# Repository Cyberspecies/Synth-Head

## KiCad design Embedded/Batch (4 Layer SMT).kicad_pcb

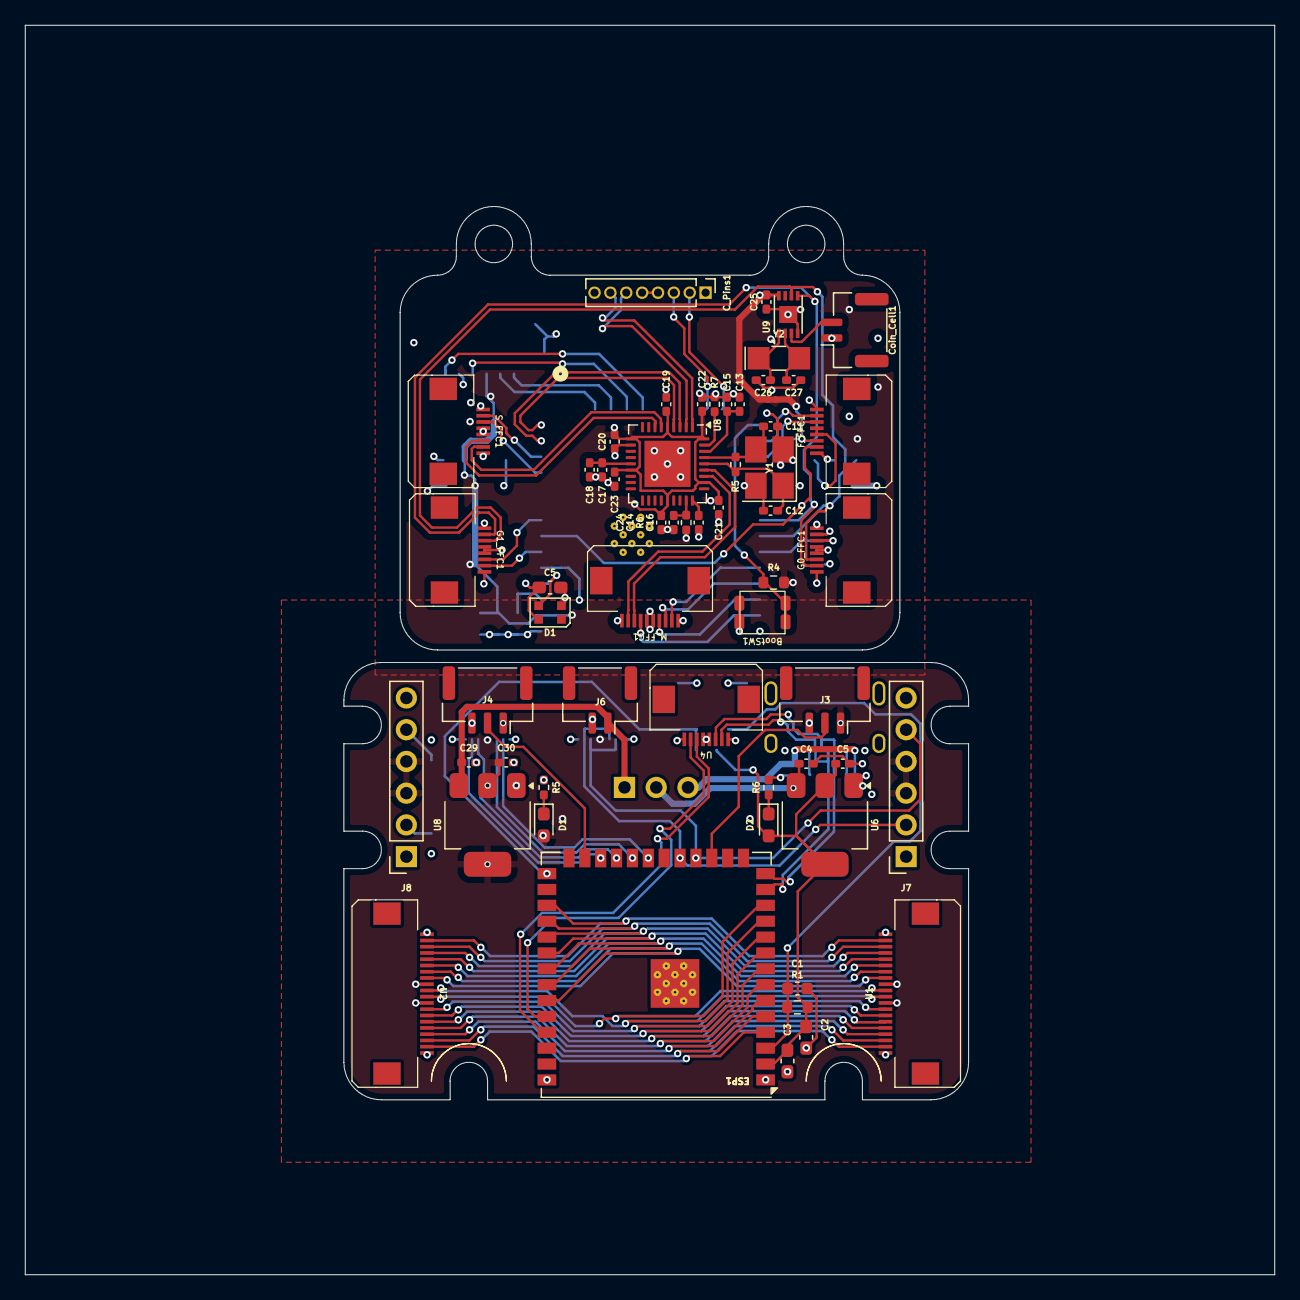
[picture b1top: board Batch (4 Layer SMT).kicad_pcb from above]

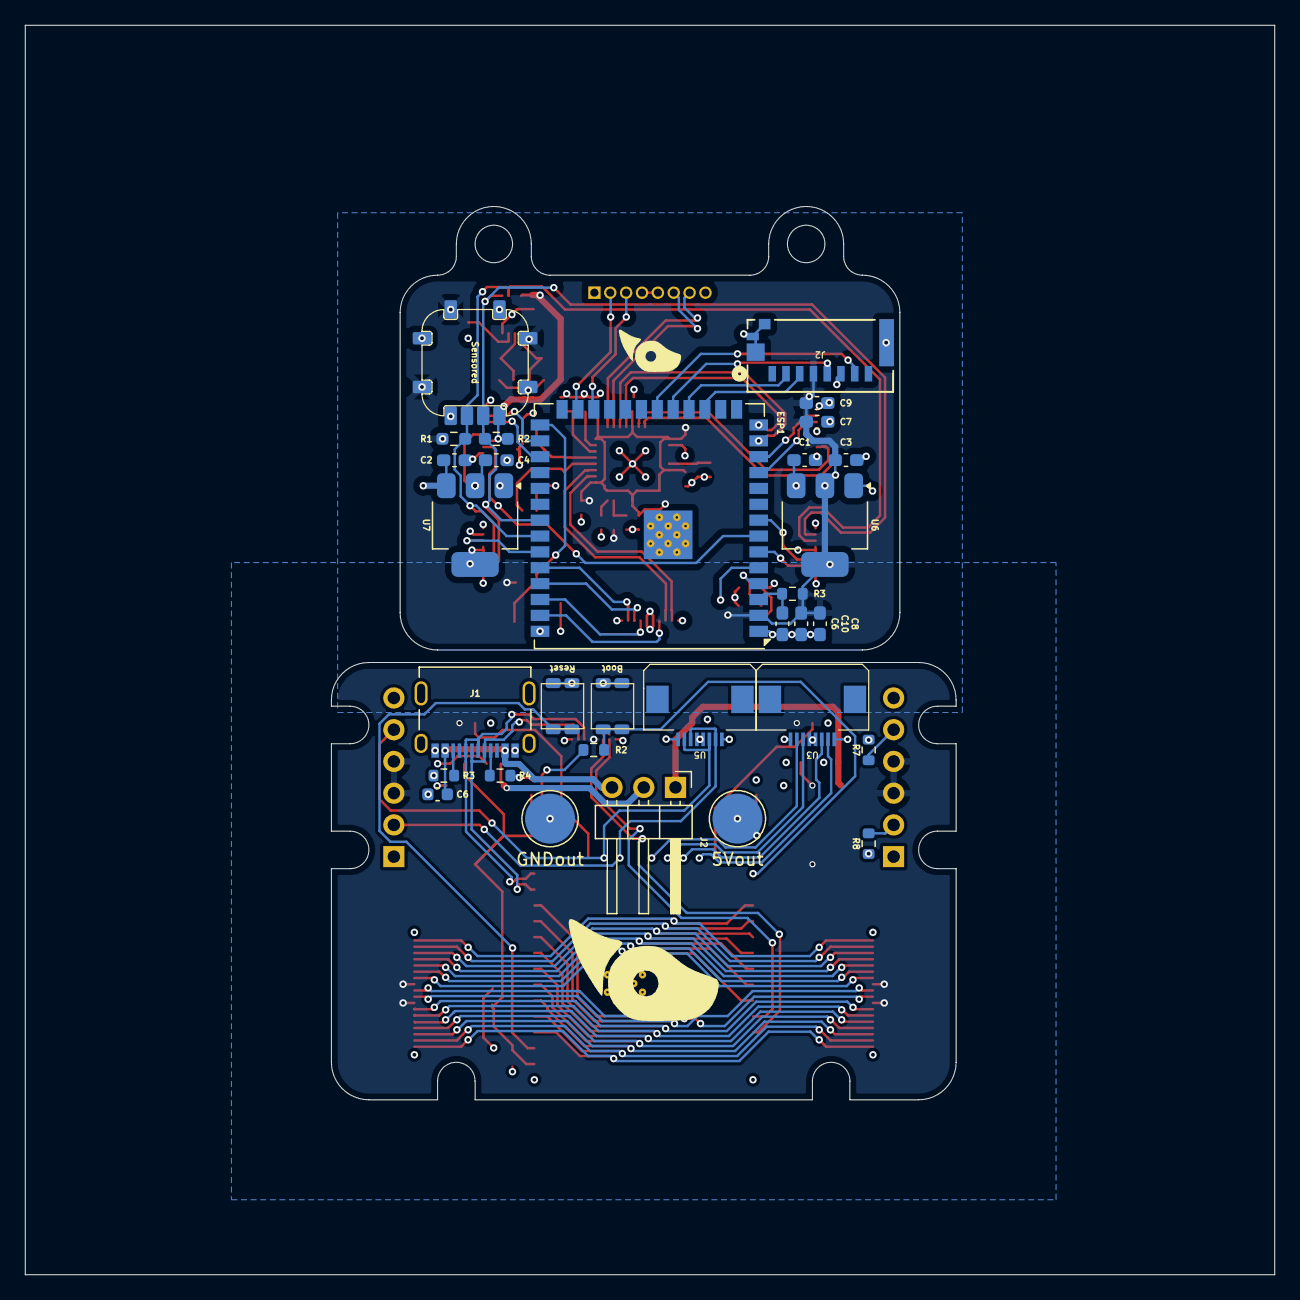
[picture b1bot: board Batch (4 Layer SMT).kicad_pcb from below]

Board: 4 copper layers, 100.0 x 100.0 mm, 89 parts (31 on the bottom side), 79 nets.

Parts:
BootSW1: SW_Push; R-667843
BootSW1#2: Boot; R-667843
C1: 1uF; C_0603_1608Metric
C1#2, C2#2: 0.1uf; C_0603_1608Metric_Pad1.08x0.95mm_HandSolder
C2, C7, C8: 22uF; C_0603_1608Metric_Pad1.08x0.95mm_HandSolder
C3, C9, C10: 0.1uF; C_0603_1608Metric_Pad1.08x0.95mm_HandSolder
C3#2, C4#2: 10uf; C_0603_1608Metric_Pad1.08x0.95mm_HandSolder
C4, C29: 0.1uf; C_0402_1005Metric_Pad0.74x0.62mm_HandSolder
C5, C30: 10uf; C_0402_1005Metric_Pad0.74x0.62mm_HandSolder
C5#2, C6: 1uF; C_0603_1608Metric_Pad1.08x0.95mm_HandSolder
C6#2: 10uF; C_0603_1608Metric
C11, C12: 18pf; C_0402_1005Metric_Pad0.74x0.62mm_HandSolder
C13, C17: 1uF; C_0402_1005Metric_Pad0.74x0.62mm_HandSolder
C14, C15, C16, C18, C19, C20, C21, C22, C23, C24, C25: 0.1uF; C_0402_1005Metric_Pad0.74x0.62mm_HandSolder
C26: 10pf; C_0402_1005Metric_Pad0.74x0.62mm_HandSolder
C27: 12pf; C_0402_1005Metric_Pad0.74x0.62mm_HandSolder
C_Pins1: C Pins; PinHeader_1x08_P1.27mm_Vertical
Coin_Cell1: Coin Cell; JST_GH_SM02B-GHS-TB_1x02-1MP_P1.25mm_Horizontal
D1, D2: LED; D_0603_1608Metric_Pad1.05x0.95mm_HandSolder
D1#2: WS2812B-2020; LED_WS2812B-2020_PLCC4_2.0x2.0mm
ESP1: ESP32-S3-WROOM-1; ESP32-S3-WROOM-1U
ESP1#2: ESP32-S3-WROOM-1U
F_FFC1: F FFC; FFC-8-0.5
G0_FFC1: G0 FFC; FFC-8-0.5
G1_FFC1: G1 FFC; FFC-8-0.5
J1: 10171746-00021LF; AMPHENOL_10171746-00021LF
J2: PWR Jumper Pins; PinHeader_1x03_P2.54mm_Horizontal
J2#2: MicroSD; MicroSD_473092651
J3: L0 JST; JST_GH_SM03B-GHS-TB_1x03-1MP_P1.25mm_Horizontal
J4: L1 JST; JST_GH_SM03B-GHS-TB_1x03-1MP_P1.25mm_Horizontal
J5: 5Vout; TestPoint_Pad_D4.0mm
J6: A JST; JST_GH_SM02B-GHS-TB_1x02-1MP_P1.25mm_Horizontal
J7: S Pins A; PinSocket_1x06_P2.54mm_Vertical
J8: S Pins B; PinSocket_1x06_P2.54mm_Vertical
J9: GNDout; TestPoint_Pad_D4.0mm
M_FFC1: M FFC; FFC-10-0.5
R1, R2#2, R3, R4: 10K; R_0603_1608Metric
R1#2, R2: 10K; R_0603_1608Metric_Pad0.98x0.95mm_HandSolder
R3#2, R4#2, R7#2, R8: 5.1K; R_0603_1608Metric
R5: 155ohm min; R_0402_1005Metric_Pad0.72x0.64mm_HandSolder
R5#2: 1M; R_0402_1005Metric_Pad0.72x0.64mm_HandSolder
R6: 100K; R_0402_1005Metric_Pad0.72x0.64mm_HandSolder
R6#2: 70ohm min; R_0402_1005Metric_Pad0.72x0.64mm_HandSolder
R7: 12K; R_0402_1005Metric_Pad0.72x0.64mm_HandSolder
RstSW1: Reset; R-667843
S_FFC1: S FFC; FFC-8-0.5
U1: D0 FFC; FFC-20-0.5
U2: D1 FFC; FFC-20-0.5
U3: U FFC; FFC-8-0.5
U4: S FFC; FFC-8-0.5
U5: R FFC; FFC-8-0.5
U6, U6#2: LD1117S33TR_SOT223; SOT-223-3_TabPin2
U7, U8#2: LD1117S50TR_SOT223; SOT-223-3_TabPin2
U8: USB2513B_Bi; QFN-36-1EP_6x6mm_P0.5mm_EP3.7x3.7mm
U9: MCP7940N-xMNY; DFN-8-1EP_3x2mm_P0.5mm_EP1.36x1.46mm
U11: Sensored
Y1: TSX-3225 24MF18X-C0; Crystal_SMD_SeikoEpson_TSX3225-4Pin_3.2x2.5mm_HandSoldering
Y2: CM7V-T1A; Crystal_SMD_MicroCrystal_CC7V-T1A-2Pin_3.2x1.5mm_HandSolder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

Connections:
+3V3: C2.1, C3.1, C3#2.1, C5.1, C7.1, C8.1, C9.1, C10.1, C19.1, C20.1, C21.1, C22.1, C23.1, C24.1, C25.1, D2.2 (A), ESP1.2 (3V3), ESP1#2.2 (3V3), F_FFC1.3, J2#2.4, R1.1, R1#2.1, R2.1, R2#2.1, R3.1, R4.1, R6.2, U6.2 (VO), U6#2.2 (VO), U8.5 (VDDA33), U8.10 (VDDA33), U8.15 (VDD33), U8.23 (VDD33), U8.29 (VDDA33), U8.36 (VDDA33), U9.8 (VCC), U11.3V3
+5V: C4#2.1, C5#2.1, C30.1, C_Pins1.4, C_Pins1.5, D1.2 (A), D1#2.4 (VDD), F_FFC1.4, F_FFC1.5, G0_FFC1.4, G0_FFC1.5, G1_FFC1.4, G1_FFC1.5, J3.1, J4.1, J5.1, J7.3, J7.4, J8.3, J8.4, S_FFC1.4, S_FFC1.5, U1.9, U1.12, U2.9, U2.12, U3.4, U3.5, U4.4, U4.5, U5.4, U5.5, U7.2 (VO), U8#2.2 (VO)
+5VP: C16.1, U8.27 (VBUS_DET)
+5VS: C1#2.1, C2#2.1, M_FFC1.5, M_FFC1.6, U6#2.3 (VI), U7.3 (VI)
+5VUSB: C6#2.1, J1.A4_B9 (VBUS_A), J1.B4_A9 (VBUS_B), J2.3
+PWR: C4.1, J2.2, U6.3 (VI)
+RAWVS: C29.1, J2.1, J6.1, U8#2.3 (VI)
Addr LED 0: ESP1.17 (GPIO9/TOUCH9/ADC1_CH8/FSPIHD/SUBSPIHD), J3.2
Addr LED 1: ESP1.25 (GPIO48/SPICLK_N/SUBSPICLK_N_DIFF), J4.2
Debug LED: D1#2.3 (DIN), ESP1#2.4 (GPIO4/TOUCH4/ADC1_CH3)
Disp GPIO 0: ESP1.4 (GPIO4/TOUCH4/ADC1_CH3), U1.2, U2.19
Disp GPIO 1: ESP1.5 (GPIO5/TOUCH5/ADC1_CH4), U1.3, U2.18
Disp GPIO 2: ESP1.6 (GPIO6/TOUCH6/ADC1_CH5), U1.4, U2.17
Disp GPIO 3: ESP1.7 (GPIO7/TOUCH7/ADC1_CH6), U1.5, U2.16
Disp GPIO 4: ESP1.8 (GPIO15/U0RTS/ADC2_CH4/XTAL_32K_P), U1.6, U2.15
Disp GPIO 5: ESP1.9 (GPIO16/U0CTS/ADC2_CH5/XTAL_32K_N), U1.7, U2.14
Disp GPIO 6: ESP1.10 (GPIO17/U1TXD/ADC2_CH6), U1.8, U2.13
Disp GPIO 7: ESP1.11 (GPIO18/U1RXD/ADC2_CH7/CLK_OUT3), U1.10, U2.10
Disp GPIO 8: ESP1.12 (GPIO8/TOUCH8/ADC1_CH7/SUBSPICS1), U1.11, U2.11
Disp GPIO 9: ESP1.35 (MTMS/GPIO42), U1.13, U2.8
Disp GPIO 10: ESP1.34 (MTDI/GPIO41/CLK_OUT1), U1.14, U2.7
Disp GPIO 11: ESP1.33 (MTDO/GPIO40/CLK_OUT2), U1.15, U2.6
Disp GPIO 12: ESP1.32 (MTCK/GPIO39/CLK_OUT3/SUBSPICS1), U1.16, U2.5
Disp GPIO 13: ESP1.31 (GPIO38/FSPIWP/SUBSPIWP), U1.17, U2.4
Disp GPIO 14: ESP1.30 (SPIDQS/GPIO37/FSPIQ/SUBSPIQ), U1.18, U2.3
Disp GPIO 15: ESP1.29 (SPIIO7/GPIO36/FSPICLK/SUBSPICLK), U1.19, U2.2
Fan 0: ESP1#2.29 (SPIIO7/GPIO36/FSPICLK/SUBSPICLK), F_FFC1.6
Fan 1: ESP1#2.28 (SPIIO6/GPIO35/FSPID/SUBSPID), F_FFC1.7
GND: BootSW1.2, BootSW1#2.2, C1.1, C1#2.2, C2.2, C2#2.2, C3.2, C3#2.2, C4.2, C4#2.2, C5.2, C5#2.2, C6.1, C6#2.2, C7.2, C8.2, C9.2, C10.2, C11.1, C12.1, C13.2, C14.2, C15.2, C16.2, C17.2, C18.2, C19.2, C20.2, C21.2, C22.2, C23.2, C24.2, C25.2, C26.2, C27.2, C29.2, C30.2, C_Pins1.1, C_Pins1.8, Coin_Cell1.1, D1#2.2 (VSS), ESP1.1 (GND), ESP1.40 (GND), ESP1.41 (GND), ESP1#2.1 (GND), ESP1#2.40 (GND), ESP1#2.41 (GND), F_FFC1.1, F_FFC1.8, G0_FFC1.1, G0_FFC1.8, G1_FFC1.1, G1_FFC1.8, J1.A1_B12 (GND_A), J1.B1_A12 (GND_B), J2#2.6, J2#2.G1, J2#2.G2, J2#2.G3, J2#2.G4, J3.3, J4.3, J6.2, J7.1, J7.6, J8.1, J8.6, J9.1, M_FFC1.1, M_FFC1.10, R3#2.2, R4#2.2, R5.2, R6#2.2, R7.1, R7#2.2, R8.2, RstSW1.2, S_FFC1.1, S_FFC1.8, U1.1, U1.20, U2.1, U2.20, U3.1, U3.8, U4.1, U4.8, U5.1, U5.8, U6.1 (GND), U6#2.1 (GND), U7.1 (GND), U8.11 (TEST), U8.37 (VSS), U8#2.1 (GND), U9.4 (VSS), U9.9 (EP), U11.GND, Y1.2, Y1.4
Gesture GPIO 1: ESP1#2.35 (MTMS/GPIO42), G0_FFC1.6
Gesture GPIO 2: ESP1#2.8 (GPIO15/U0RTS/ADC2_CH4/XTAL_32K_P), G1_FFC1.6
HUD UART RX: C_Pins1.2, ESP1#2.25 (GPIO48/SPICLK_N/SUBSPICLK_N_DIFF)
HUD UART TX: C_Pins1.3, ESP1#2.24 (GPIO47/SPICLK_P/SUBSPICLK_P_DIFF)
HUD USB +: C_Pins1.6, U8.2 (USBDP_DN1/PRT_DIS_P1)
HUD USB -: C_Pins1.7, U8.1 (USBDM_DN1/PRT_DIS_M1)
I2C SCL: ESP1.18 (GPIO10/TOUCH10/ADC1_CH9/FSPICS0/FSPIIO4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), ESP1#2.34 (MTDI/GPIO41/CLK_OUT1), G0_FFC1.3, G1_FFC1.3, J7.5, R1#2.2, U5.3, U5.7, U9.6 (SCL), U11.SCL
I2C SDA: ESP1.19 (GPIO11/TOUCH11/ADC2_CH0/FSPID/FSPIIO5/S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), ESP1#2.33 (MTDO/GPIO40/CLK_OUT2), G0_FFC1.2, G1_FFC1.2, J7.2, R2.2, U5.2, U5.6, U9.5 (SDA), U11.SDA
Main UART RX: ESP1.36 (U0RXD/GPIO44/CLK_OUT2), U4.7
Main UART TX: ESP1.37 (U0TXD/GPIO43/CLK_OUT1), U4.6
Main USB +: ESP1.14 (GPIO20/U1CTS/ADC2_CH9/CLK_OUT1/USB_D+), ESP1#2.14 (GPIO20/U1CTS/ADC2_CH9/CLK_OUT1/USB_D+), J1.A6 (DP1), J1.B6 (DP2), U4.3, U8.4 (USBDP_DN2/PRT_DIS_P2)
Main USB -: ESP1.13 (GPIO19/U1RTS/ADC2_CH8/CLK_OUT2/USB_D-), ESP1#2.13 (GPIO19/U1RTS/ADC2_CH8/CLK_OUT2/USB_D-), J1.A7 (DN1), J1.B7 (DN2), U4.2, U8.3 (USBDM_DN2/PRT_DIS_M2)
Mic Analog: ESP1#2.7 (GPIO7/TOUCH7/ADC1_CH6), F_FFC1.2
unnamed: Coin_Cell1.2, U9.3 (VBAT)
unnamed: D1.1 (K), R5.1
unnamed: D2.1 (K), R6#2.1
unnamed: C1.2, C6.2, ESP1.3 (EN), ESP1#2.3 (EN), R1.2, R3.2, RstSW1.1
unnamed: BootSW1.1, BootSW1#2.1, ESP1.27 (GPIO0/BOOT), ESP1#2.27 (GPIO0/BOOT), R2#2.2, R4.2
unnamed: J1.A5 (CC1), R4#2.1
unnamed: J1.B5 (CC2), R3#2.1
unnamed: J8.2, R8.1
unnamed: J8.5, R7#2.1
unnamed: C17.1, C18.1, U8.14 (CRFILT)
unnamed: C13.1, C15.1, U8.34 (PLLFILT)
unnamed: R7.2, U8.35 (RBIAS)
unnamed: C14.1, R6.1, U8.26 (RESET_N)
unnamed: C11.2, R5#2.2, U8.33 (XTALIN/CLKIN), Y1.3
unnamed: C12.2, R5#2.1, U8.32 (XTALOUT), Y1.1
unnamed: C26.1, U9.1 (X1), Y2.1
unnamed: C27.1, U9.2 (X2), Y2.2
Photoresistor 1: ESP1#2.5 (GPIO5/TOUCH5/ADC1_CH4), G0_FFC1.7
Photoresistor 2: ESP1#2.6 (GPIO6/TOUCH6/ADC1_CH5), G1_FFC1.7
Power GPIO 0: ESP1#2.38 (GPIO2/TOUCH2/ADC1_CH1), M_FFC1.4
Power GPIO 1: ESP1#2.39 (GPIO1/TOUCH1/ADC1_CH0), M_FFC1.7
Power UART RX: ESP1#2.36 (U0RXD/GPIO44/CLK_OUT2), M_FFC1.2
Power UART TX: ESP1#2.37 (U0TXD/GPIO43/CLK_OUT1), M_FFC1.3
Power USB +: M_FFC1.8, U8.31 (USBDP_UP)
Power USB -: M_FFC1.9, U8.30 (USBDM_UP)
SD SPI CLK: ESP1#2.19 (GPIO11/TOUCH11/ADC2_CH0/FSPID/FSPIIO5/S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), J2#2.5
SD SPI CS: ESP1#2.18 (GPIO10/TOUCH10/ADC1_CH9/FSPICS0/FSPIIO4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), J2#2.2
SD SPI MISO: ESP1#2.20 (GPIO12/TOUCH12/ADC2_CH1/FSPICLK/FSPIIO6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), J2#2.7
SD SPI MOSI: ESP1#2.17 (GPIO9/TOUCH9/ADC1_CH8/FSPIHD/SUBSPIHD), J2#2.3
Snoot UART RX: ESP1#2.12 (GPIO8/TOUCH8/ADC1_CH7/SUBSPICS1), S_FFC1.2
Snoot UART TX: ESP1#2.11 (GPIO18/U1RXD/ADC2_CH7/CLK_OUT3), S_FFC1.3
Snoot USB +: S_FFC1.6, U8.7 (USBDP_DN3/PRT_DIS_P3)
Snoot USB -: S_FFC1.7, U8.6 (USBDM_DN3/PRT_DIS_M3)
UI GPIO 0: ESP1.24 (GPIO47/SPICLK_P/SUBSPICLK_P_DIFF), U3.2
UI GPIO 1: ESP1.23 (GPIO21), U3.3
UI GPIO 2: ESP1.22 (GPIO14/TOUCH14/ADC2_CH3/FSPIWP/FSPIDQS/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), U3.6
UI GPIO 3: ESP1.21 (GPIO13/TOUCH13/ADC2_CH2/FSPIQ/FSPIIO7/S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), U3.7

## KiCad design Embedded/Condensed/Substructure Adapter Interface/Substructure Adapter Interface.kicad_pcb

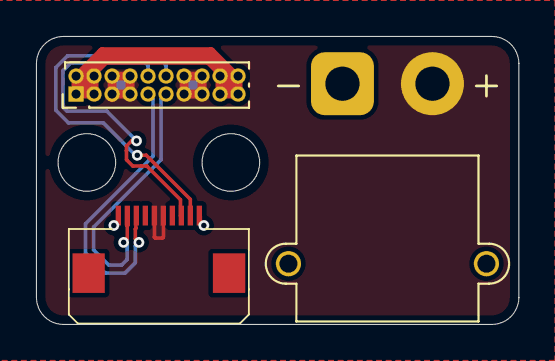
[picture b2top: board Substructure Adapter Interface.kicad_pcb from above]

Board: 2 copper layers, 26.8 x 16.0 mm, 3 parts (0 on the bottom side), 6 nets.

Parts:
J1: Conn_01x02_Socket; AMASS_XT30PW-M_1x02_P2.50mm_Horizontal
J2: Conn_02x10_Odd_Even; PinHeader_2x10_P1.00mm_Vertical
U1: FFC 0.8mm 10P

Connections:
+RAWVS: J1.2, J2.5, J2.6, J2.7, J2.8, J2.13, J2.14, J2.15, J2.16, U1.5, U1.6
GND: J1.1, J2.1, J2.2, J2.3, J2.4, J2.17, J2.18, J2.19, J2.20, U1.1, U1.10
Power UART RX: J2.12, U1.9
Power UART TX: J2.10, U1.8
Power USB +: J2.9, U1.3
Power USB -: J2.11, U1.2

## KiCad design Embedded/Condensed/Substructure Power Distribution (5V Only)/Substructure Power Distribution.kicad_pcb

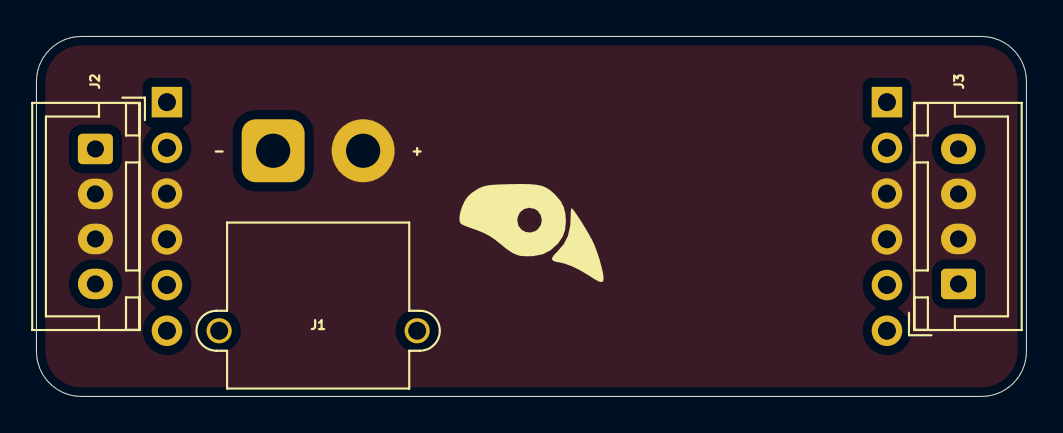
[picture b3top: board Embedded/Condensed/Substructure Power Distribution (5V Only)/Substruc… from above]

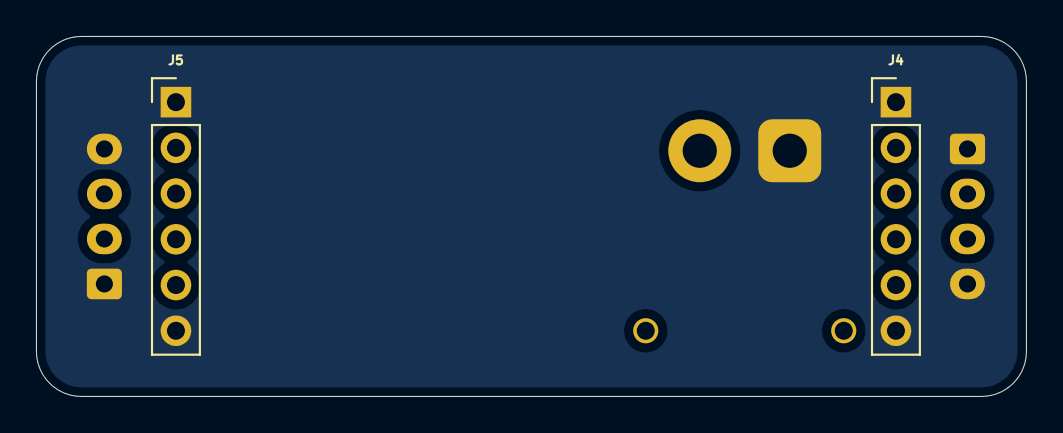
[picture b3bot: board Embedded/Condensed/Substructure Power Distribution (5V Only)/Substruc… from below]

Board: 2 copper layers, 55.0 x 20.0 mm, 5 parts (2 on the bottom side), 2 nets, no tracks yet.

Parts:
J1: S JST; AMASS_XT30PW-M_1x02_P2.50mm_Horizontal
J2: D0 FFC; JST_XH_B4B-XH-A_1x04_P2.50mm_Vertical
J3: D1 FFC; JST_XH_B4B-XH-A_1x04_P2.50mm_Vertical
J4: S Pins A; PinHeader_1x06_P2.54mm_Vertical
J5: S Pins B; PinHeader_1x06_P2.54mm_Vertical

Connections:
+5V: J1.2, J2.2, J2.3, J3.2, J3.3, J4.3, J4.4, J5.3, J5.4
GND: J1.1, J2.1, J2.4, J3.1, J3.4, J4.1, J4.6, J5.1, J5.6

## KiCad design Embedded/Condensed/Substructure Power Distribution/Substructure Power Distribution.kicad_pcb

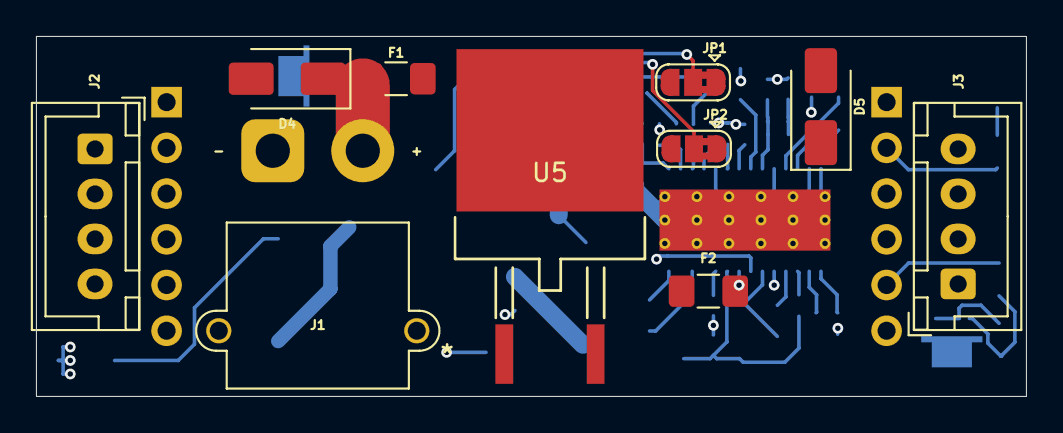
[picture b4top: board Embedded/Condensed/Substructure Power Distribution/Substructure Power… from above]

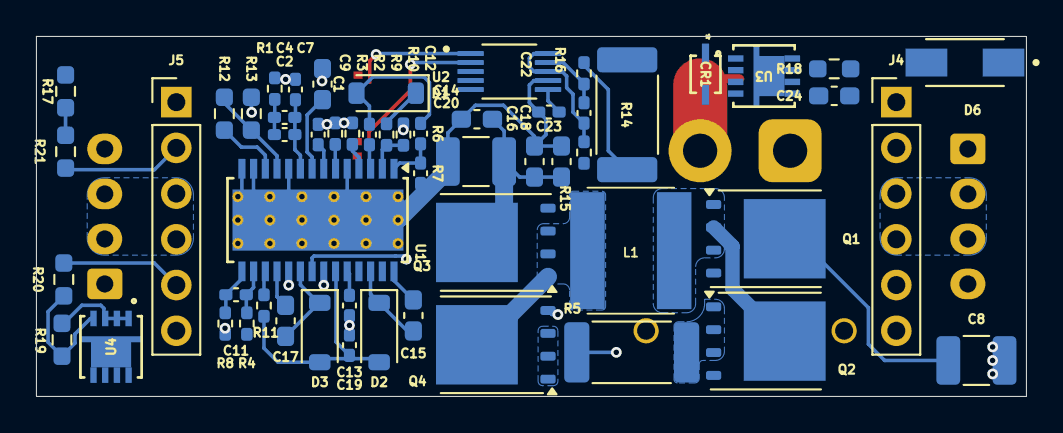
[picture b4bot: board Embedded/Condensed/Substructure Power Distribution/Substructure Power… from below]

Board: 4 copper layers, 55.0 x 20.0 mm, 66 parts (56 on the bottom side), 45 nets.

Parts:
C1: 12nF 0ohm; C_0603_1608Metric_Pad1.08x0.95mm_HandSolder
C2, C4: 6.8nF 523mohm; C_0402_1005Metric_Pad0.74x0.62mm_HandSolder
C7: 2nF 0ohm; C_0402_1005Metric_Pad0.74x0.62mm_HandSolder
C8, C20: 47uF 3mohm; C_1210_3225Metric_Pad1.33x2.70mm_HandSolder
C9: 82pF 0ohm; C_0402_1005Metric_Pad0.74x0.62mm_HandSolder
C11: 47pF 1mohms; C_0402_1005Metric_Pad0.74x0.62mm_HandSolder
C12: 100nF 39mohm; R_0402_1005Metric_Pad0.72x0.64mm_HandSolder
C13: 100nF 1mohm; C_0402_1005Metric_Pad0.74x0.62mm_HandSolder
C14, C16, C18: 22uF 3.71mohm; C_0603_1608Metric_Pad1.08x0.95mm_HandSolder
C15, C17: 100nF 50mohm; C_0603_1608Metric_Pad1.08x0.95mm_HandSolder
C19: 1uF 11.4mohm; C_0402_1005Metric_Pad0.74x0.62mm_HandSolder
C22: 1uF; C_0402_1005Metric_Pad0.74x0.62mm_HandSolder
C23: 0.1uF; C_0402_1005Metric_Pad0.74x0.62mm_HandSolder
C24: 0.1uF; C_0603_1608Metric_Pad1.08x0.95mm_HandSolder
CR1: BZT52C6V2S-7-F; SOD323_DIO
D1, D2, D3: 385mV 500mA; D_SOD-123
D4, D5: SMAJ26A; D_SMA
D6: 1SMA5919BT3G; DIOM5226X220N
F1, F2: Fuse; Fuse_1206_3216Metric_Pad1.42x1.75mm_HandSolder
J1: S JST; AMASS_XT30PW-M_1x02_P2.50mm_Horizontal
J2: D0 FFC; JST_XH_B4B-XH-A_1x04_P2.50mm_Vertical
J3: D1 FFC; JST_XH_B4B-XH-A_1x04_P2.50mm_Vertical
J4: S Pins A; PinHeader_1x06_P2.54mm_Vertical
J5: S Pins B; PinHeader_1x06_P2.54mm_Vertical
JP1, JP2: Bit Set; SolderJumper-3_P1.3mm_Bridged2Bar12_RoundedPad1.0x1.5mm
L1: 1uH 2.6mohm; XAL7070-102ME
Q1, Q2, Q4: CSD17577Q5A; TDSON-8-1
Q3: CSD17573Q5B; TDSON-8-1
R1: 732; R_0402_1005Metric_Pad0.72x0.64mm_HandSolder
R2: 93.1K; R_0402_1005Metric_Pad0.72x0.64mm_HandSolder
R3: 13K; R_0402_1005Metric_Pad0.72x0.64mm_HandSolder
R4, R8: 100; R_0402_1005Metric_Pad0.72x0.64mm_HandSolder
R5: 5m; R_2512_6332Metric_Pad1.40x3.35mm_HandSolder
R6: 249K; C_0402_1005Metric_Pad0.74x0.62mm_HandSolder
R7: 110K; C_0402_1005Metric_Pad0.74x0.62mm_HandSolder
R9: 2K; C_0402_1005Metric_Pad0.74x0.62mm_HandSolder
R10, R15, R16: 10; R_0402_1005Metric_Pad0.72x0.64mm_HandSolder
R11: 10K; R_0402_1005Metric_Pad0.72x0.64mm_HandSolder
R12: 105K; R_0603_1608Metric_Pad0.98x0.95mm_HandSolder
R13: 20K; R_0603_1608Metric_Pad0.98x0.95mm_HandSolder
R14: Shunt CRF2512-FZ-R002ELF; R_2512_6332Metric_Pad1.40x3.35mm_HandSolder
R17: 100K; R_0603_1608Metric_Pad0.98x0.95mm_HandSolder
R18, R19: 10K; R_0603_1608Metric_Pad0.98x0.95mm_HandSolder
R20, R21: 1M; R_0603_1608Metric_Pad0.98x0.95mm_HandSolder
U1: LM5176PWP; HTSSOP-28-1EP_4.4x9.7mm_P0.65mm_EP3.4x9.5mm_ThermalVias
U2: INA220AIDGSR; SOP50P490X110-10N
U3, U4: SI7111EDN-T1-GE3; MOSFET_0DN-T1-GE3_VIS
U5: TN5015H-6G-TR; D2PAK_T2550_STM-M

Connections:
+3V3: C23.1, JP1.3 (B), JP2.3 (B), U2.6 (VS)
+5V: D5.1 (A1), J2.2, J2.3, J3.2, J3.3, J4.3, J4.4, J5.3, J5.4, R19.1, U4.1 (S), U4.2 (S), U4.3 (S)
+5VP: C14.1, C16.1, C18.1, C20.1, F2.1, Q3.5 (D), R12.1, U1.12 (VOSNS)
+RAWVK: CR1.1, R14.1, R15.1, U3.1 (S), U3.2 (S), U3.3 (S)
+RAWVP: C8.1, D1.2 (A), Q1.5 (D), R6.1, R9.1, R14.2, R16.1
+RAWVS: D4.1 (A1), F1.1, J1.2
EN 1: J5.2, R21.1
EN 2: J5.5, R20.2
GND: C1.2, C7.2, C8.2, C9.2, C12.2, C13.2, C14.2, C16.2, C18.2, C19.2, C20.2, C23.2, C24.2, D4.2 (A2), D5.2 (A2), J1.1, J2.1, J2.4, J3.1, J3.4, J4.1, J4.6, J5.1, J5.6, JP1.1 (A), JP2.1 (A), R1.2, R2.2, R3.2, R5.2, R7.2, R8.2, R13.2, R17.2, R18.2, U1.5 (DITH), U1.10 (AGND), U1.13 (ISNS(-)), U1.14 (ISNS(+)), U1.22 (PGND), U1.29 (PowerPAD), U2.7 (GND), U5.1 (K)
I2C SCL: J4.5, U2.5 (SCL)
I2C SDA: J4.2, U2.4 (SDA)
unnamed: C2.2, C4.2, R1.1
unnamed: D1.1 (K), R10.1
unnamed: C19.1, D2.2 (A), D3.2 (A), R11.1, U1.23 (VCC)
unnamed: C15.1, D2.1 (K), U1.26 (BOOT1)
unnamed: C17.1, D3.1 (K), U1.20 (BOOT2)
unnamed: F1.2, U3.5 (D), U3.6 (D), U3.7 (D), U3.8 (D)
unnamed: JP1.2 (C), U2.1 (A1)
unnamed: JP2.2 (C), U2.2 (A0)
unnamed: Q1.4 (G), U1.27 (HDRV1)
unnamed: C15.2, L1.1, Q1.1 (S), Q1.2 (S), Q1.3 (S), Q2.5 (D), U1.28 (SW1)
unnamed: Q2.4 (G), U1.25 (LDRV1)
unnamed: Q2.1 (S), Q2.2 (S), Q2.3 (S), Q4.1 (S), Q4.2 (S), Q4.3 (S), R4.2, R5.1
unnamed: Q3.4 (G), U1.19 (HDRV2)
unnamed: C17.2, L1.2, Q3.1 (S), Q3.2 (S), Q3.3 (S), Q4.5 (D), U1.18 (SW2)
unnamed: Q4.4 (G), U1.21 (LDRV2)
unnamed: C13.1, U1.24 (BIAS)
unnamed: C2.1, C4.1, C7.1, U1.9 (COMP)
unnamed: C11.1, R4.1, U1.16 (CS)
unnamed: C11.2, R8.1, U1.15 (CSG)
unnamed: R6.2, R7.1, U1.1 (EN/UVLO)
unnamed: R12.2, R13.1, U1.11 (FB)
unnamed: R2.1, U1.4 (MODE)
unnamed: R11.2, U1.17 (PGOOD)
unnamed: R3.1, U1.6 (RT/SYNC)
unnamed: C9.1, U1.7 (SLOPE)
unnamed: C1.1, U1.8 (SS)
unnamed: C12.1, R10.2, U1.2 (VIN)
unnamed: R9.2, U1.3 (VISNS)
unnamed: C22.1, R15.2, U2.8 (VBUS), U2.10 (VIN+)
unnamed: C22.2, R16.2, U2.9 (VIN-)
unnamed: CR1.2, R17.1, R21.2, U3.4 (G)
unnamed: R19.2, R20.1, U4.4 (G)
unnamed: D6.C, F2.2, U4.5 (D), U4.6 (D), U4.7 (D), U4.8 (D), U5.2 (A)
unnamed: C24.1, D6.A, R18.1, U5.3 (G)

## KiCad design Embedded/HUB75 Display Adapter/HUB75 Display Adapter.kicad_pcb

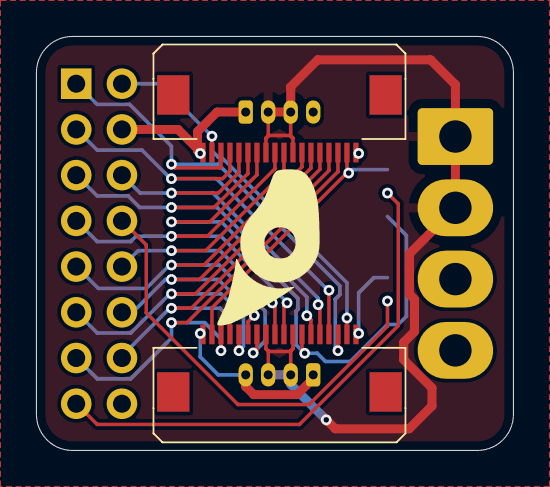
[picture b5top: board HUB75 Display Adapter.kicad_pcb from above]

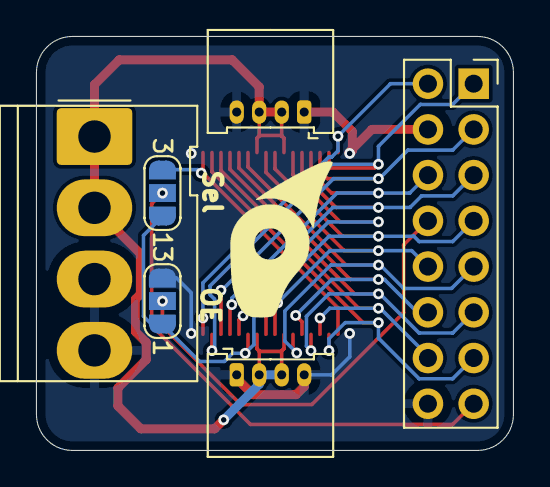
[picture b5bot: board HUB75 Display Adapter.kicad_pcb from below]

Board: 2 copper layers, 26.5 x 23.0 mm, 8 parts (6 on the bottom side), 18 nets.

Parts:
J1: HUB75 Input; PinSocket_2x08_P2.54mm_Vertical
J2: Vertical; Molex_KK-396_5273-04A_1x04_P3.96mm_Vertical
J3, J4: JST [D]; Molex_PicoBlade_53048-0410_1x04_P1.25mm_Horizontal
JP1: No E for OE Alt; SolderJumper-3_P1.3mm_Open_RoundedPad1.0x1.5mm_NumberLabels
JP2: Panel Selector; SolderJumper-3_P1.3mm_Open_RoundedPad1.0x1.5mm_NumberLabels
U1: Input A; FFC Aliexpress 0.5mm 18P
U2: Input B; FFC Aliexpress 0.5mm 18P

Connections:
+5V: J2.1, J2.2, J3.2, J3.3, J4.2, J4.3, U1.8, U1.11, U2.8, U2.11
GND: J1.4, J1.16, J2.3, J2.4, J3.1, J3.4, J4.1, J4.4, JP1.3 (B), U1.1, U1.18, U2.1, U2.18
HUB75 A: J1.9, U1.7, U2.7
HUB75 B: J1.10, U1.9, U2.9
HUB75 B0: J1.3, U1.15, U2.15
HUB75 B1: J1.7, U1.10, U2.10
HUB75 C: J1.11, U1.5, U2.5
HUB75 CLK: J1.13, U1.3, U2.3
HUB75 D: J1.12, U1.6, U2.6
HUB75 E: J1.8, JP1.2 (C)
HUB75 E / OE 1: JP1.1 (A), JP2.1 (A), U1.12, U2.12
HUB75 G0: J1.2, U1.17, U2.17
HUB75 G1: J1.6, U1.14, U2.14
HUB75 LAT: J1.14, U1.4, U2.4
HUB75 OE: J1.15, JP2.2 (C)
HUB75 OE / OE 0: JP2.3 (B), U1.2, U2.2
HUB75 R0: J1.1, U1.16, U2.16
HUB75 R1: J1.5, U1.13, U2.13

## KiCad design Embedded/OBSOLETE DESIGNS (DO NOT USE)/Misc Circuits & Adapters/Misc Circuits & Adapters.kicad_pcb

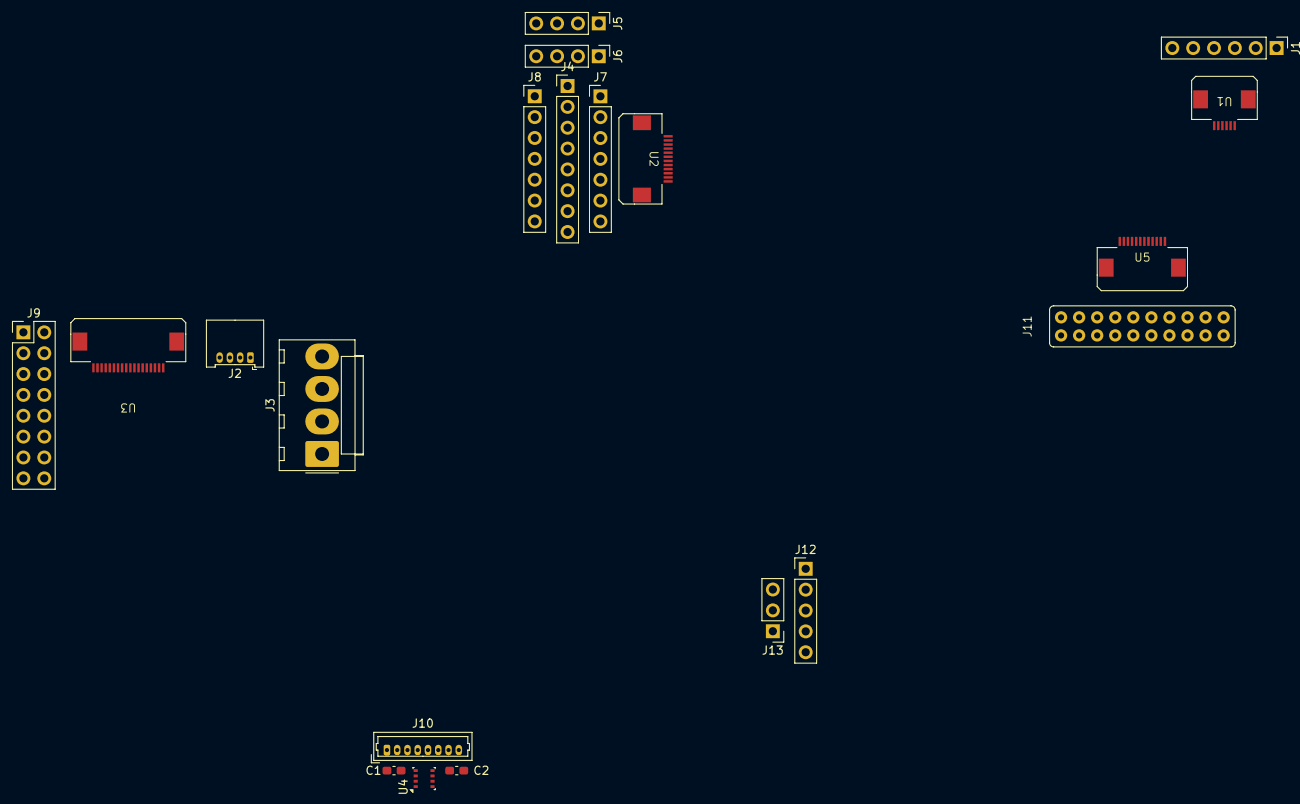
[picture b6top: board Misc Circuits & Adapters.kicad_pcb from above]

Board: 2 copper layers, 20 parts (0 on the bottom side), 35 nets, no tracks yet.

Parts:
C1, C2: 100nF; C_0603_1608Metric_Pad1.08x0.95mm_HandSolder
J1: VL53L0X; PinHeader_1x06_P2.54mm_Vertical
J2: JST [D]; Molex_PicoBlade_53048-0410_1x04_P1.25mm_Horizontal
J3: HUB75 PWR; Molex_KK-396_A-41791-0004_1x04_P3.96mm_Vertical
J4: 2.0 IPS Display; PinHeader_1x08_P2.54mm_Vertical
J5, J6: I2C OLED; PinHeader_1x04_P2.54mm_Vertical
J7, J8: SPI OLED; PinHeader_1x07_P2.54mm_Vertical
J9: HUB75; PinHeader_2x08_P2.54mm_Vertical
J10: JST [S]; Molex_PicoBlade_53047-0810_1x08_P1.25mm_Vertical
J11: Pogo Pins; 2.2mm 20P
J12: Jaw Pogo Cable; PinHeader_1x05_P2.54mm_Vertical
J13: To LEDS; PinHeader_1x03_P2.54mm_Vertical
U1: FFC [C]; FFC Aliexpress 0.5mm 6P
U2: FFC [U]; FFC Aliexpress 0.5mm 12P
U3: FFC [D]; FFC Aliexpress 0.5mm 18P
U4: BME280; Bosch_LGA-8_2.5x2.5mm_P0.65mm_ClockwisePinNumbering
U5: FFC [G]; FFC Aliexpress 0.5mm 12P

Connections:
+3V3: C1.2, C2.1, J1.1, J10.3, J10.6, U1.3, U4.2 (CSB), U4.6 (VDDIO), U4.8 (VDD)
+5V: J2.2, J2.3, J3.2, J3.3, J4.7, J5.4, J6.3, J7.1, J8.6, J11.9, J11.10, J11.11, J11.12, J12.3, J13.1, U2.5, U2.8, U3.8, U3.11, U5.5, U5.8
CPU-GPU GPIO 0: J11.3, U5.2
CPU-GPU GPIO 1: J11.4, U5.4
CPU-GPU GPIO 2: J11.17, U5.9
CPU-GPU GPIO 3: J11.18, U5.11
CPU-GPU RX: J11.6, U5.6
CPU-GPU TX: J11.15, U5.7
Disp 0: J9.1, U3.2
Disp 1: J9.3, U3.3
Disp 2: J9.5, U3.4
Disp 3: J9.7, U3.5
Disp 4: J9.9, U3.6
Disp 5: J9.11, U3.7
Disp 6: J9.13, U3.12
Disp 7: J9.2, U3.13
Disp 8: J9.6, U3.14
Disp 9: J9.8, U3.15
Disp 10: J9.10, U3.16
Disp 11: J9.12, U3.17
Disp RX: J9.14, U3.9
Disp TX: J9.15, U3.10
GND: C1.1, C2.2, J1.2, J2.1, J2.4, J3.1, J3.4, J4.8, J5.3, J6.4, J7.2, J8.7, J9.4, J9.16, J10.1, J10.2, J10.7, J10.8, J11.1, J11.2, J11.5, J11.7, J11.8, J11.13, J11.14, J11.16, J11.19, J11.20, J12.1, J12.5, J13.3, U1.1, U1.6, U2.1, U2.3, U2.10, U2.12, U3.1, U3.18, U4.1 (GND), U4.5 (SDO), U4.7 (GND), U5.1, U5.3, U5.10, U5.12
unnamed: J12.2, J12.4, J13.2
Snoot SCL: J10.4, U4.4 (SCK)
Snoot SDA: J10.5, U4.3 (SDI)
TOF SCL: J1.3, U1.5
TOF SDA: J1.4, U1.2
UI 0: J4.1, J7.3, J8.5, U2.2
UI 1: J4.2, J7.4, J8.4, U2.4
UI 2: J4.5, J7.7, J8.3, U2.9
UI 3: J4.6, J8.2, U2.11
UI IO 0: J4.3, J5.2, J6.2, J7.5, J8.1, U2.6
UI IO 1: J4.4, J5.1, J6.1, J7.6, U2.7
XShut: J1.6, U1.4
